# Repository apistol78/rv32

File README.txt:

TODO
----

- UART with QM-Tech board.
- Parallell LCD display with QM-Tech board.
- Audio on Terasic board.
- Audio on QM-Tech board.
- USB-host PICO.

STATS
-----

12264 (42%)

https://www.intel.com/content/dam/www/programmable/us/en/pdfs/literature/hb/external-memory/emi.pdf
https://itectec.com/electrical/electronic-alteras-dram-controller-with-uniphy/

https://mindchasers.com/dev/rv-getting-started

quake-k210

../configure --prefix=/opt/rv32-imf --with-arch=rv32imf --with-abi=ilp32

SDRAM
24 bit address
32 bit word

20000000 - 20FFFFFF

16777215 words

536870912 bytes => 512 MByte

Winbond SDRAM, W9825G6KH-6
W9864G6JT

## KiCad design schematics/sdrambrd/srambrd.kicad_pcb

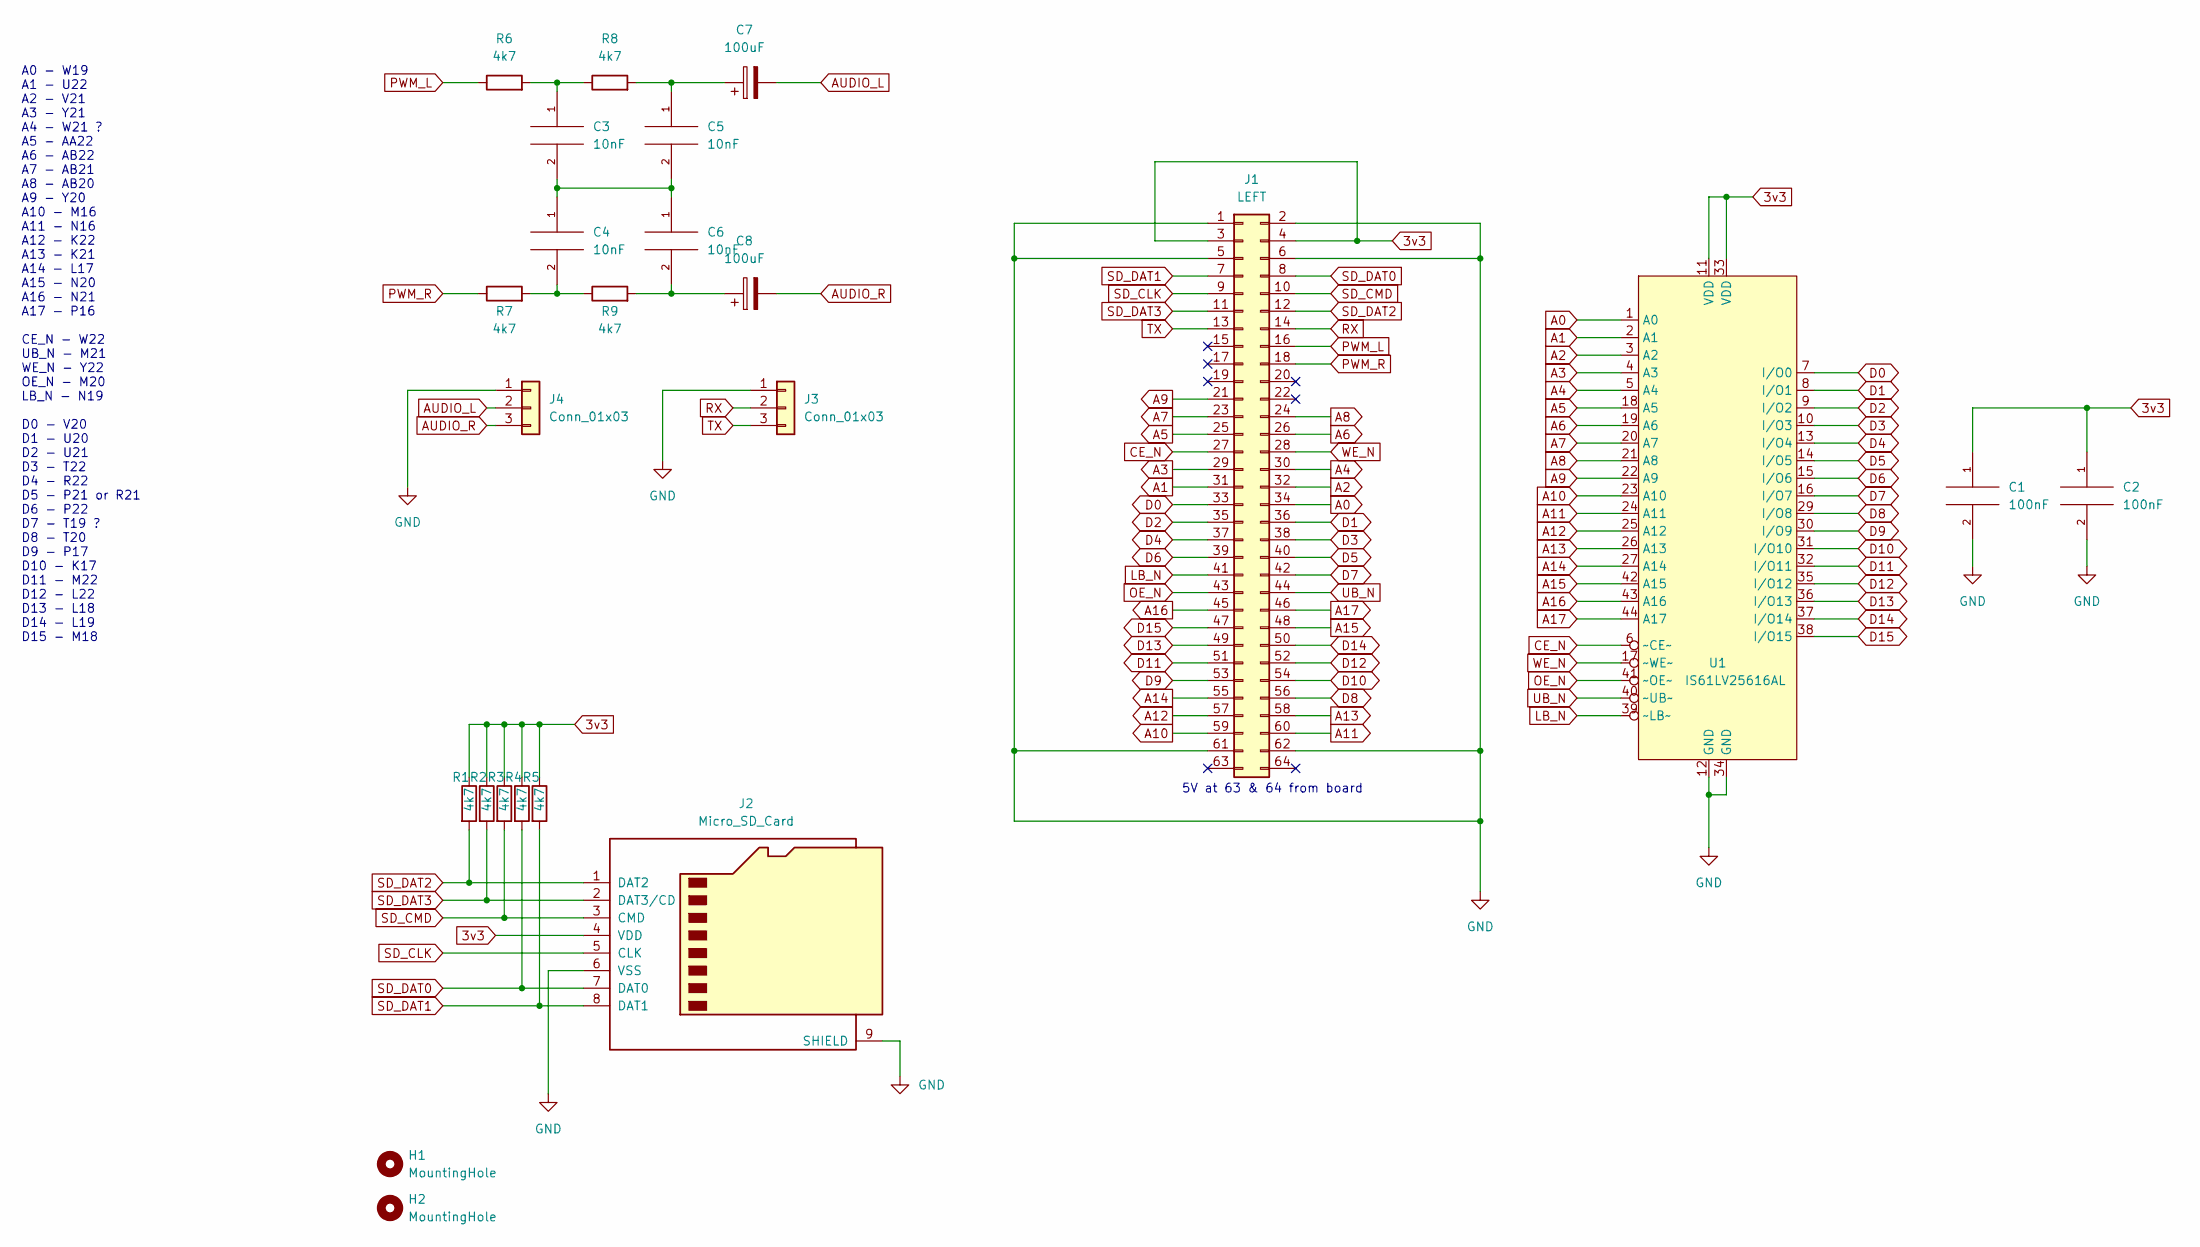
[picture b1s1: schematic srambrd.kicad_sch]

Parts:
C1, C2: 100nF; C_0805_2012Metric_Pad1.18x1.45mm_HandSolder
C3, C4, C5, C6: 10nF; C_0805_2012Metric_Pad1.18x1.45mm_HandSolder
C7, C8: 100uF; CP_Elec_5x5.3
H1, H2: MountingHole; MountingHole_3.2mm_M3_DIN965_Pad
J1: LEFT; PinSocket_2x32_P2.54mm_Vertical
J2: Micro_SD_Card; microSD_HC_Hirose_DM3D-SF
J3, J4: Conn_01x03; PinHeader_1x03_P2.54mm_Vertical
R1, R2, R3, R4, R5, R6, R7, R8, R9: 4k7; R_0805_2012Metric_Pad1.20x1.40mm_HandSolder
U1: IS61LV25616AL; TSOP-II-44_10.16x18.41mm_P0.8mm

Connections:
3v3: C1.1, C2.1, J1.3, J1.4, J2.4 (VDD), R1.1, R2.1, R3.1, R4.1, R5.1, U1.11 (VDD), U1.33 (VDD)
A0: J1.34, U1.1 (A0)
A1: J1.31, U1.2 (A1)
A2: J1.32, U1.3 (A2)
A3: J1.29, U1.4 (A3)
A4: J1.30, U1.5 (A4)
A5: J1.25, U1.18 (A5)
A6: J1.26, U1.19 (A6)
A7: J1.23, U1.20 (A7)
A8: J1.24, U1.21 (A8)
A9: J1.21, U1.22 (A9)
A10: J1.59, U1.23 (A10)
A11: J1.60, U1.24 (A11)
A12: J1.57, U1.25 (A12)
A13: J1.58, U1.26 (A13)
A14: J1.55, U1.27 (A14)
A15: J1.48, U1.42 (A15)
A16: J1.45, U1.43 (A16)
A17: J1.46, U1.44 (A17)
AUDIO_L: C7.2, J4.2
AUDIO_R: C8.2, J4.3
CE_N: J1.27, U1.6 (~CE~)
D0: J1.33, U1.7 (I/O0)
D1: J1.36, U1.8 (I/O1)
D2: J1.35, U1.9 (I/O2)
D3: J1.38, U1.10 (I/O3)
D4: J1.37, U1.13 (I/O4)
D5: J1.40, U1.14 (I/O5)
D6: J1.39, U1.15 (I/O6)
D7: J1.42, U1.16 (I/O7)
D8: J1.56, U1.29 (I/O8)
D9: J1.53, U1.30 (I/O9)
D10: J1.54, U1.31 (I/O10)
D11: J1.51, U1.32 (I/O11)
D12: J1.52, U1.35 (I/O12)
D13: J1.49, U1.36 (I/O13)
D14: J1.50, U1.37 (I/O14)
D15: J1.47, U1.38 (I/O15)
GND: C1.2, C2.2, J1.1, J1.2, J1.5, J1.6, J1.61, J1.62, J2.6 (VSS), J2.9 (SHIELD), J3.1, J4.1, U1.12 (GND), U1.34 (GND)
LB_N: J1.41, U1.39 (~LB~)
unnamed: C3.1, R6.2, R8.1
unnamed: C3.2, C4.1, C5.2, C6.1
unnamed: C4.2, R7.2, R9.1
unnamed: C5.1, C7.1, R8.2
unnamed: C6.2, C8.1, R9.2
OE_N: J1.43, U1.41 (~OE~)
PWM_L: J1.16, R6.1
PWM_R: J1.18, R7.1
RX: J1.14, J3.2
SD_CLK: J1.9, J2.5 (CLK)
SD_CMD: J1.10, J2.3 (CMD), R3.2
SD_DAT0: J1.8, J2.7 (DAT0), R4.2
SD_DAT1: J1.7, J2.8 (DAT1), R5.2
SD_DAT2: J1.12, J2.1 (DAT2), R1.2
SD_DAT3: J1.11, J2.2 (DAT3/CD), R2.2
TX: J1.13, J3.3
UB_N: J1.44, U1.40 (~UB~)
WE_N: J1.28, U1.17 (~WE~)

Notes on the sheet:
5V at 63 & 64 from board
A0 - W19 A1 - U22 A2 - V21 A3 - Y21 A4 - W21 ? A5 - AA22 A6 - AB22 A7 - AB21 A8 - AB20 A9 - Y20 A10 - M16 A11 - N16 A12 - K22 A13 - K21 A14 - L17 A15 - N20 A16 - N21 A17 - P16 CE_N - W22 UB_N - M21 WE_N - Y22 OE_N - M20 LB_N - N19 D0 - V20 D1 - U20 D2 - U21 D3 - T22 D4 - R22 D5 - P21 or R21 D6 - P2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

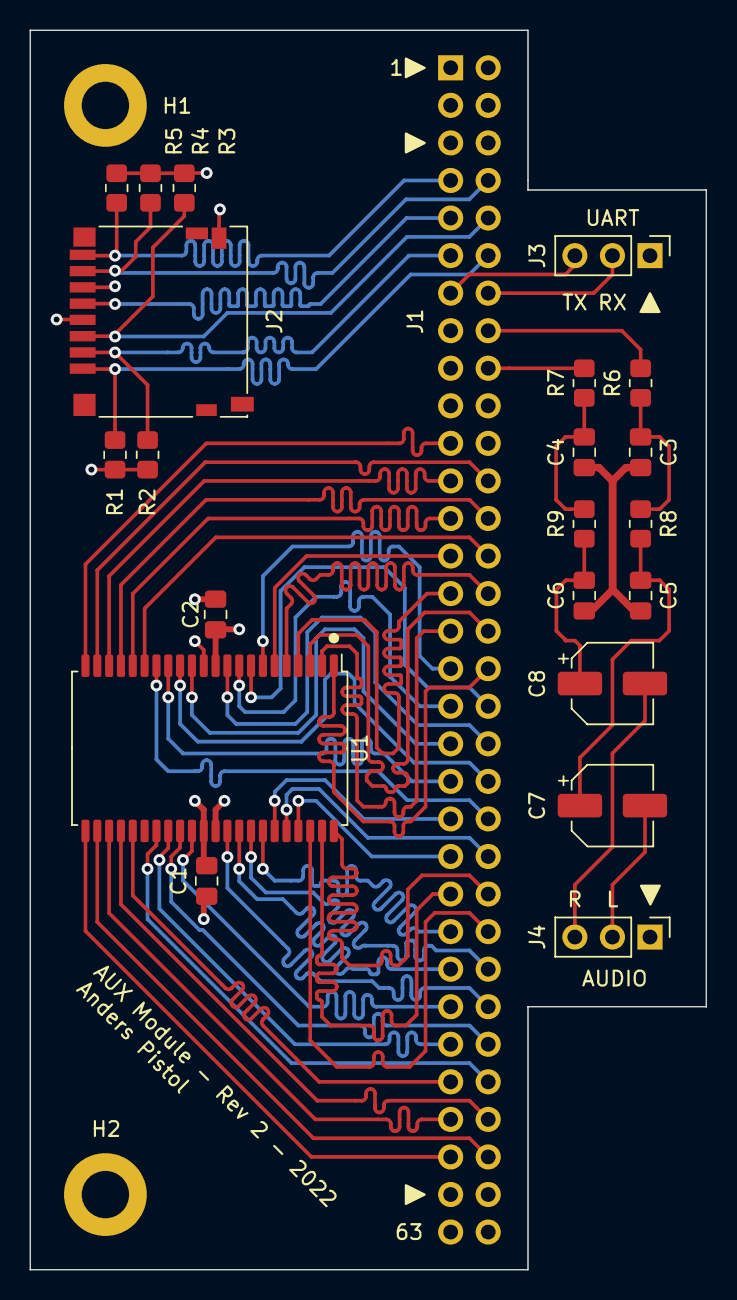
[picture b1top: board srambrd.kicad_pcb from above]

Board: 4 copper layers, 45.7 x 83.8 mm, 24 parts (1 on the bottom side), 58 nets.

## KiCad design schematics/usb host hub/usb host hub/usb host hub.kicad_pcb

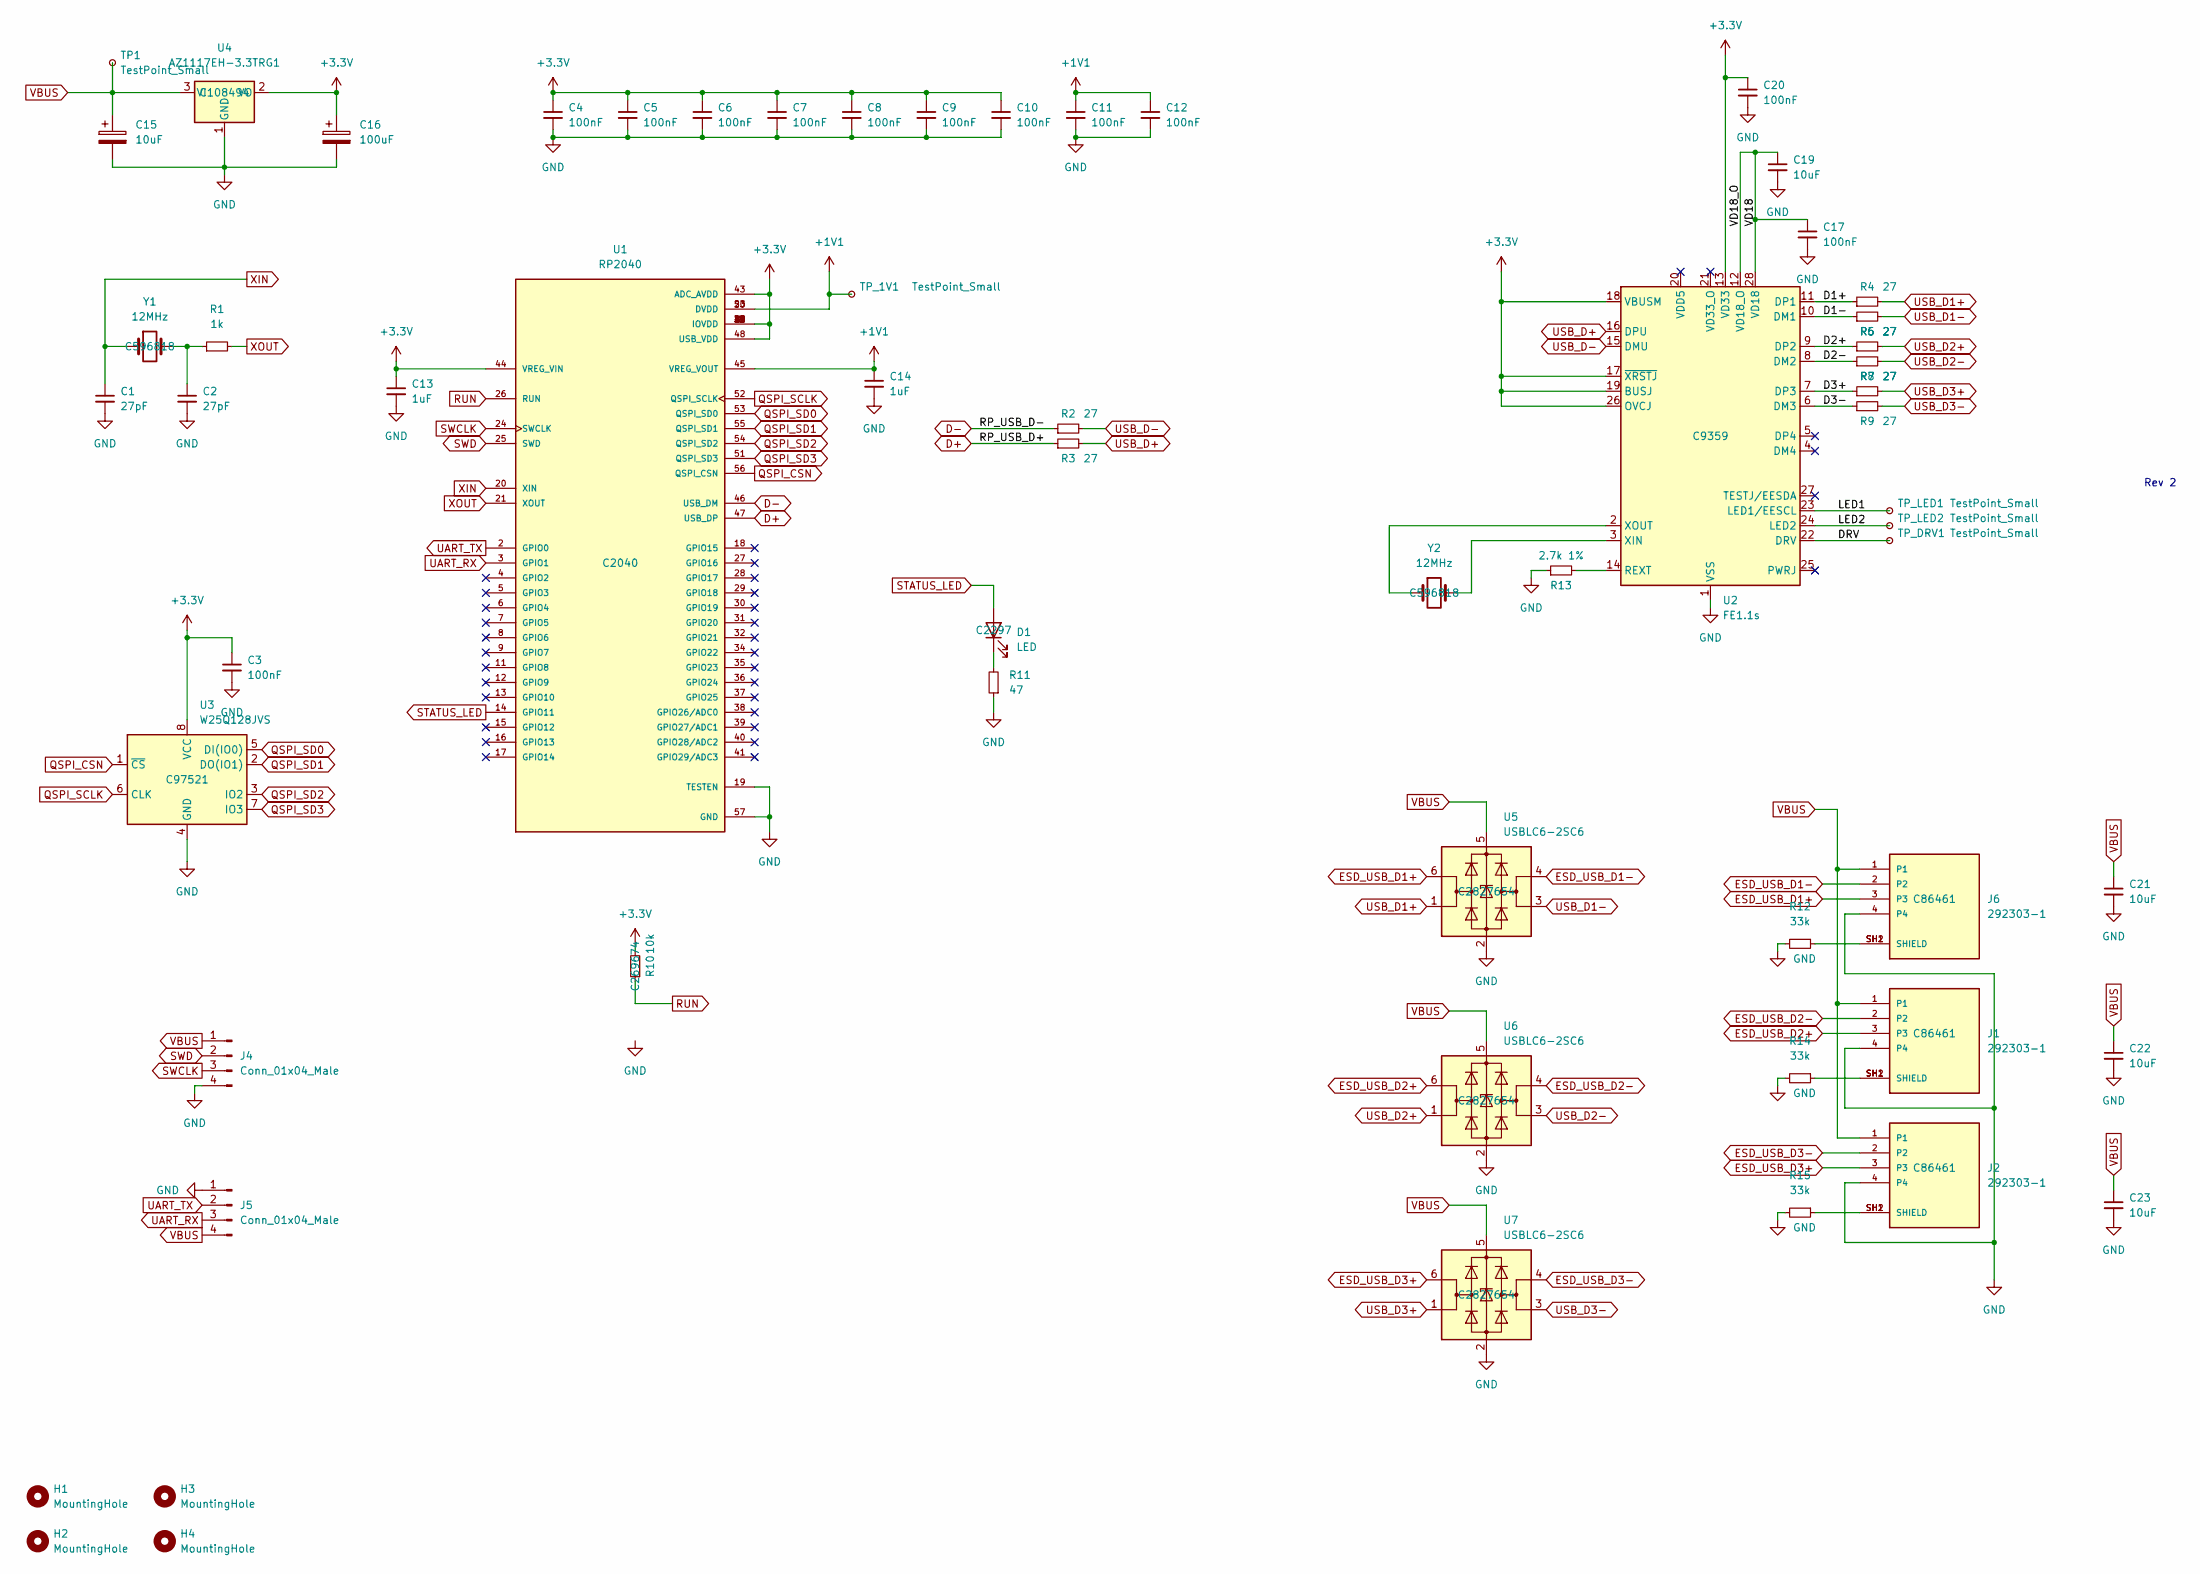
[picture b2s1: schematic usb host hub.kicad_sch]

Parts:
C1, C2: 27pF; C_0805_2012Metric
C3, C4, C5, C6, C7, C8, C9, C10, C11, C12, C17, C20: 100nF; C_0402_1005Metric; LCSC C307331
C13, C14: 1uF; C_0402_1005Metric
C15: 10uF; CP_Elec_5x5.3
C16: 100uF; CP_Elec_5x5.3
C19: 10uF; C_0402_1005Metric
C21, C22, C23: 10uF; C_0805_2012Metric
D1: LED; LED_0805_2012Metric; LCSC C2297
H1, H2, H3, H4: MountingHole; MountingHole_3.2mm_M3_DIN965_Pad
J1, J2, J6: 292303-1; TE_292303-1
J4: Conn_01x04_Male; PinHeader_1x04_P2.54mm_Vertical
J5: Conn_01x04_Male; JST_EH_B4B-EH-A_1x04_P2.50mm_Vertical
R1: 1k; R_0805_2012Metric
R2, R3: 27; R_0805_2012Metric
R4, R5, R6, R7, R8, R9: 27; R_0402_1005Metric
R10: 10k; R_0402_1005Metric; LCSC C269674
R11: 47; R_0805_2012Metric
R12, R14, R15: 33k; R_0805_2012Metric
R13: 2.7k 1%; R_0402_1005Metric; LCSC C25885
TP1: TestPoint_Small; TestPoint_Pad_D1.5mm
TP_1V1: TestPoint_Small; TestPoint_Pad_D1.5mm
TP_DRV1: TestPoint_Small; TestPoint_Pad_D1.5mm
TP_LED1, TP_LED2: TestPoint_Small; TestPoint_Pad_D1.5mm
U1: RP2040; QFN40P700X700X90-57N; PARTREV 1.6.1; LCSC C2040
U2: FE1.1s; SSOP-28_3.9x9.9mm_P0.635mm; LCSC C9359
U3: W25Q128JVS; SOIC-8_5.23x5.23mm_P1.27mm; LCSC C97521
U4: AZ1117EH-3.3TRG1; SOT-223-3_TabPin2; LCSC C108494
U5, U6, U7: USBLC6-2SC6; SOT-23-6
Y1, Y2: 12MHz; Crystal_SMD_HC49-SD

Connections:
+1V1: C11.1, C12.1, C14.1, TP_1V1.1, U1.23 (DVDD), U1.45 (VREG_VOUT), U1.50 (DVDD)
+3V3: C3.1, C4.1, C5.1, C6.1, C7.1, C8.1, C9.1, C10.1, C13.1, C16.1, C20.1, R10.2, U1.1 (IOVDD), U1.10 (IOVDD), U1.22 (IOVDD), U1.33 (IOVDD), U1.42 (IOVDD), U1.43 (ADC_AVDD), U1.44 (VREG_VIN), U1.48 (USB_VDD), U1.49 (IOVDD), U2.13 (VD33), U2.17 (~XRSTJ), U2.18 (VBUSM), U2.19 (BUSJ), U2.26 (OVCJ), U3.8 (VCC), U4.2 (VO)
/D1+: R4.1, U2.11 (DP1)
/D1-: R5.1, U2.10 (DM1)
/D2+: R6.1, U2.9 (DP2)
/D2-: R7.1, U2.8 (DM2)
/D3+: R8.1, U2.7 (DP3)
/D3-: R9.1, U2.6 (DM3)
/DRV: TP_DRV1.1, U2.22 (DRV)
/LED1: TP_LED1.1, U2.23 (LED1/EESCL)
/LED2: TP_LED2.1, U2.24 (LED2)
/VD18: C17.1, C19.1, U2.12 (VD18_O), U2.28 (VD18)
D+: R3.1, U1.47 (USB_DP)
D-: R2.1, U1.46 (USB_DM)
ESD_USB_D1+: J6.3, U5.6 (I/O1)
ESD_USB_D1-: J6.2, U5.4 (I/O2)
ESD_USB_D2+: J1.3, U6.6 (I/O1)
ESD_USB_D2-: J1.2, U6.4 (I/O2)
ESD_USB_D3+: J2.3, U7.6 (I/O1)
ESD_USB_D3-: J2.2, U7.4 (I/O2)
GND: C1.2, C2.2, C3.2, C4.2, C5.2, C6.2, C7.2, C8.2, C9.2, C10.2, C11.2, C12.2, C13.2, C14.2, C15.2, C16.2, C17.2, C19.2, C20.2, C21.2, C22.2, C23.2, J1.4, J2.4, J4.4, J5.1, J6.4, R11.1, R12.2, R13.1, R14.2, R15.2, U1.19 (TESTEN), U1.57 (GND), U2.1 (VSS), U3.4 (GND), U4.1 (GND), U5.2 (GND), U6.2 (GND), U7.2 (GND)
unnamed: C2.1, R1.1, Y1.2
unnamed: D1.1 (K), R11.2
unnamed: J1.SH1 (SHIELD), J1.SH2 (SHIELD), R14.1
unnamed: J2.SH1 (SHIELD), J2.SH2 (SHIELD), R15.1
unnamed: J6.SH1 (SHIELD), J6.SH2 (SHIELD), R12.1
unnamed: R13.2, U2.14 (REXT)
unnamed: U2.3 (XIN), Y2.2
unnamed: U2.2 (XOUT), Y2.1
QSPI_CSN: U1.56 (QSPI_CSN), U3.1 (~CS)
QSPI_SCLK: U1.52 (QSPI_SCLK), U3.6 (CLK)
QSPI_SD0: U1.53 (QSPI_SD0), U3.5 (DI(IO0))
QSPI_SD1: U1.55 (QSPI_SD1), U3.2 (DO(IO1))
QSPI_SD2: U1.54 (QSPI_SD2), U3.3 (IO2)
QSPI_SD3: U1.51 (QSPI_SD3), U3.7 (IO3)
RUN: R10.1, U1.26 (RUN)
STATUS_LED: D1.2 (A), U1.14 (GPIO11)
SWCLK: J4.3, U1.24 (SWCLK)
SWD: J4.2, U1.25 (SWD)
UART_RX: J5.3, U1.3 (GPIO1)
UART_TX: J5.2, U1.2 (GPIO0)
USB_D1+: R4.2, U5.1 (I/O1)
USB_D1-: R5.2, U5.3 (I/O2)
USB_D2+: R6.2, U6.1 (I/O1)
USB_D2-: R7.2, U6.3 (I/O2)
USB_D3+: R8.2, U7.1 (I/O1)
USB_D3-: R9.2, U7.3 (I/O2)
USB_D+: R3.2, U2.16 (DPU)
USB_D-: R2.2, U2.15 (DMU)
VBUS: C15.1, C21.1, C22.1, C23.1, J1.1, J2.1, J4.1, J5.4, J6.1, TP1.1, U4.3 (VI), U5.5 (VBUS), U6.5 (VBUS), U7.5 (VBUS)
XIN: C1.1, U1.20 (XIN), Y1.1
XOUT: R1.2, U1.21 (XOUT)

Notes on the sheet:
Rev 2

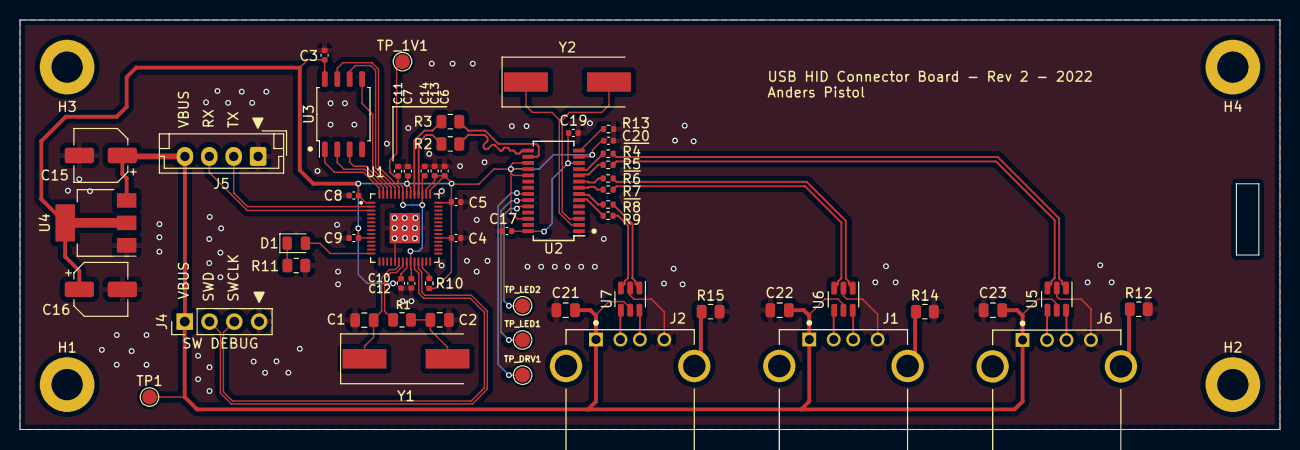
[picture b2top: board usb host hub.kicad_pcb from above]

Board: 2 copper layers, 129.0 x 41.9 mm, 61 parts (0 on the bottom side), 52 nets.

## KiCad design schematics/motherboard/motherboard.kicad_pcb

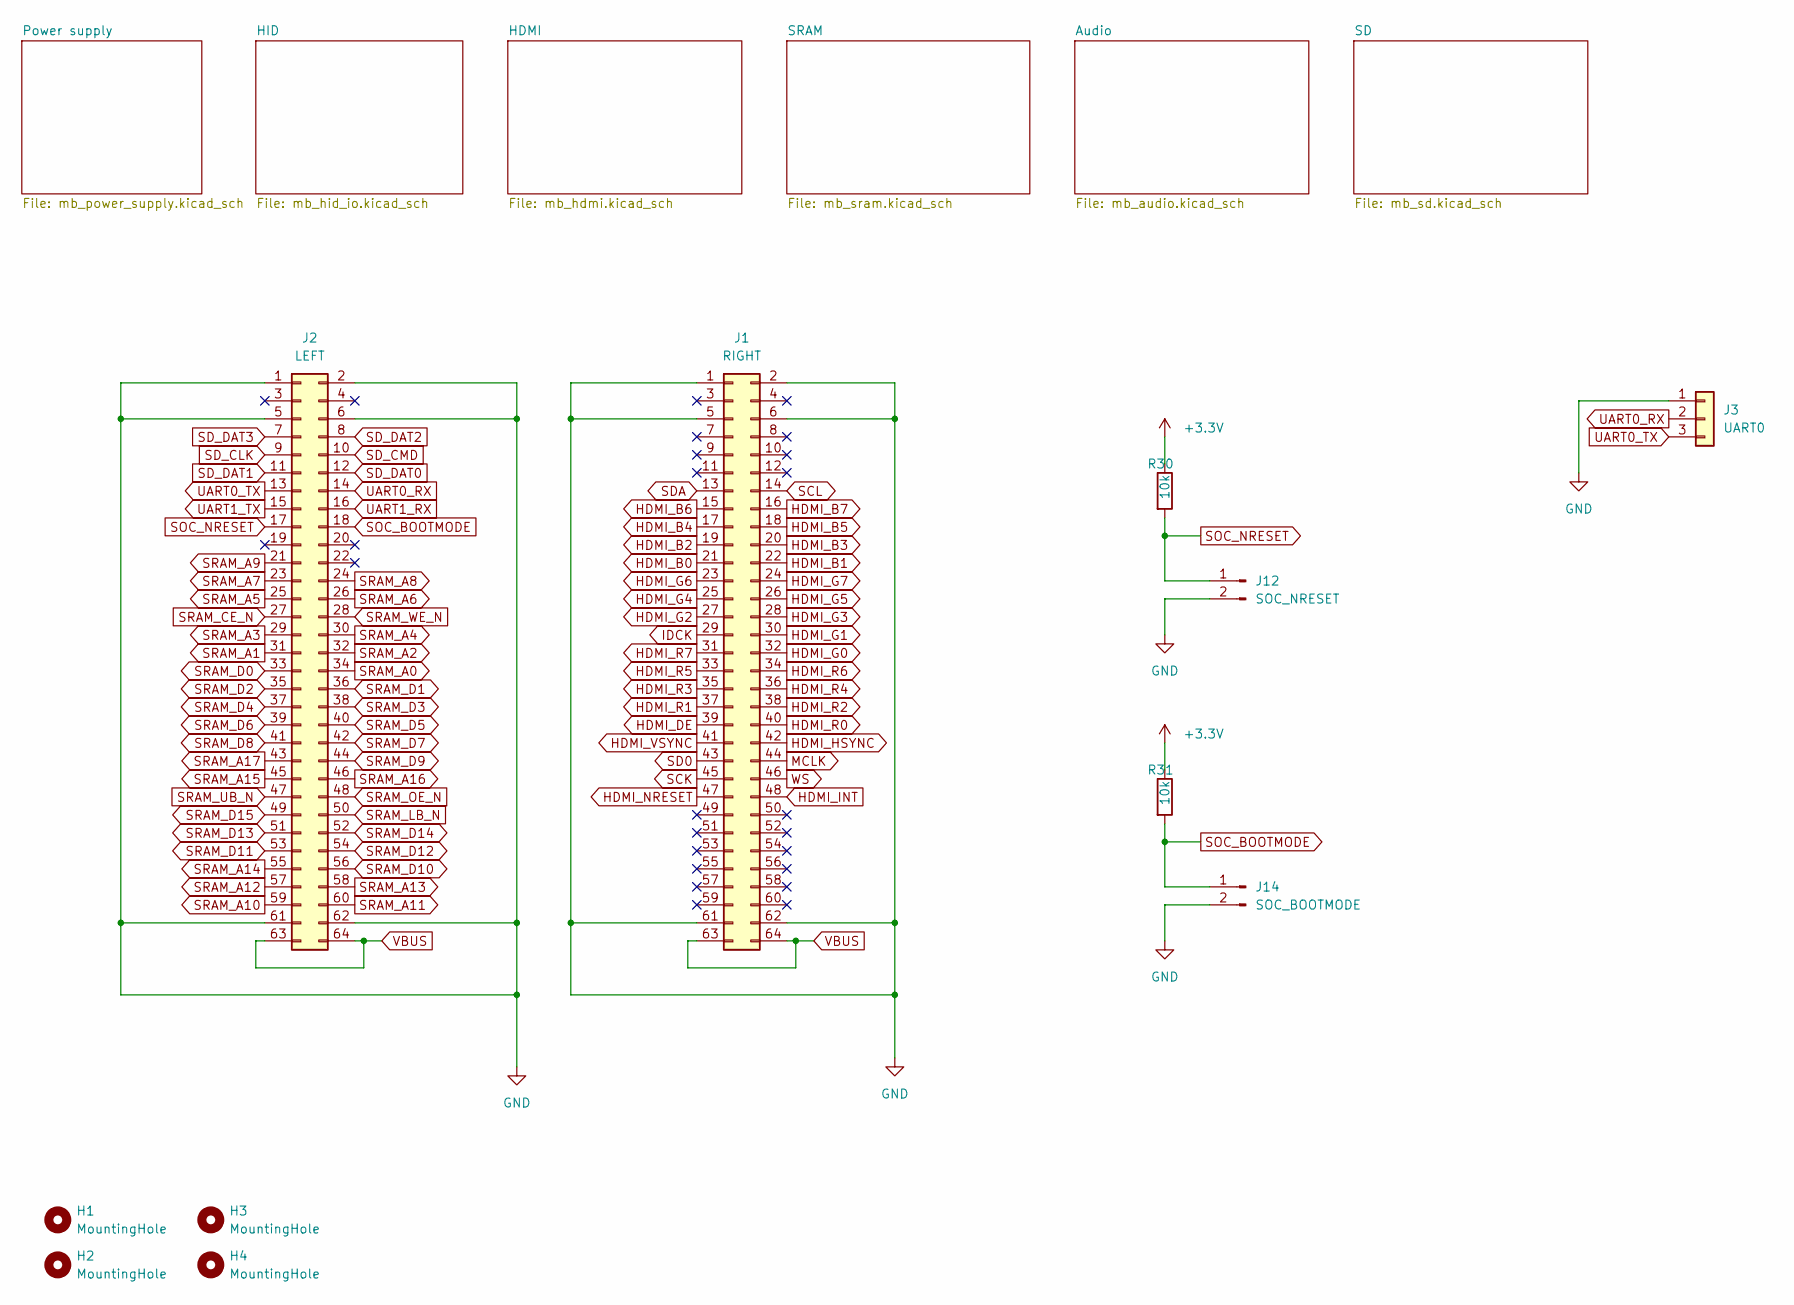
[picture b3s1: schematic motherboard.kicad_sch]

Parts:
H1, H2, H3, H4: MountingHole; MountingHole_3.2mm_M3_Pad_Via
J1: RIGHT; PinSocket_2x32_P2.54mm_Vertical
J2: LEFT; PinSocket_2x32_P2.54mm_Vertical
J3: UART0; PinHeader_1x03_P2.54mm_Vertical
J12: SOC_NRESET; PinHeader_1x02_P2.54mm_Vertical
J14: SOC_BOOTMODE; PinHeader_1x02_P2.54mm_Vertical
R30, R31: 10k; R_0805_2012Metric_Pad1.20x1.40mm_HandSolder

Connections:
+3V3: R30.1, R31.1; also elsewhere on the board
GND: J1.1, J1.2, J1.5, J1.6, J1.61, J1.62, J2.1, J2.2, J2.5, J2.6, J2.61, J2.62, J3.1, J12.2, J14.2; also elsewhere on the board
HDMI_B0: J1.21; also elsewhere on the board
HDMI_B1: J1.22; also elsewhere on the board
HDMI_B2: J1.19; also elsewhere on the board
HDMI_B3: J1.20; also elsewhere on the board
HDMI_B4: J1.17; also elsewhere on the board
HDMI_B5: J1.18; also elsewhere on the board
HDMI_B6: J1.15; also elsewhere on the board
HDMI_B7: J1.16; also elsewhere on the board
HDMI_DE: J1.39; also elsewhere on the board
HDMI_G0: J1.32; also elsewhere on the board
HDMI_G1: J1.30; also elsewhere on the board
HDMI_G2: J1.27; also elsewhere on the board
HDMI_G3: J1.28; also elsewhere on the board
HDMI_G4: J1.25; also elsewhere on the board
HDMI_G5: J1.26; also elsewhere on the board
HDMI_G6: J1.23; also elsewhere on the board
HDMI_G7: J1.24; also elsewhere on the board
HDMI_HSYNC: J1.42; also elsewhere on the board
HDMI_INT: J1.48; also elsewhere on the board
HDMI_NRESET: J1.47; also elsewhere on the board
HDMI_R0: J1.40; also elsewhere on the board
HDMI_R1: J1.37; also elsewhere on the board
HDMI_R2: J1.38; also elsewhere on the board
HDMI_R3: J1.35; also elsewhere on the board
HDMI_R4: J1.36; also elsewhere on the board
HDMI_R5: J1.33; also elsewhere on the board
HDMI_R6: J1.34; also elsewhere on the board
HDMI_R7: J1.31; also elsewhere on the board
HDMI_VSYNC: J1.41; also elsewhere on the board
IDCK: J1.29; also elsewhere on the board
MCLK: J1.44; also elsewhere on the board
SCK: J1.45; also elsewhere on the board
SCL: J1.14; also elsewhere on the board
SD0: J1.43; also elsewhere on the board
SDA: J1.13; also elsewhere on the board
SD_CLK: J2.9; also elsewhere on the board
SD_CMD: J2.10; also elsewhere on the board
SD_DAT0: J2.12; also elsewhere on the board
SD_DAT1: J2.11; also elsewhere on the board
SD_DAT2: J2.8; also elsewhere on the board
SD_DAT3: J2.7; also elsewhere on the board
SOC_BOOTMODE: J2.18, J14.1, R31.2
SOC_NRESET: J2.17, J12.1, R30.2
SRAM_A0: J2.34; also elsewhere on the board
SRAM_A1: J2.31; also elsewhere on the board
SRAM_A2: J2.32; also elsewhere on the board
SRAM_A3: J2.29; also elsewhere on the board
SRAM_A4: J2.30; also elsewhere on the board
SRAM_A5: J2.25; also elsewhere on the board
SRAM_A6: J2.26; also elsewhere on the board
SRAM_A7: J2.23; also elsewhere on the board
SRAM_A8: J2.24; also elsewhere on the board
SRAM_A9: J2.21; also elsewhere on the board
SRAM_A10: J2.59; also elsewhere on the board
SRAM_A11: J2.60; also elsewhere on the board
SRAM_A12: J2.57; also elsewhere on the board
SRAM_A13: J2.58; also elsewhere on the board
SRAM_A14: J2.55; also elsewhere on the board
SRAM_A15: J2.45; also elsewhere on the board
SRAM_A16: J2.46; also elsewhere on the board
SRAM_A17: J2.43; also elsewhere on the board
SRAM_CE_N: J2.27; also elsewhere on the board
SRAM_D0: J2.33; also elsewhere on the board
SRAM_D1: J2.36; also elsewhere on the board
SRAM_D2: J2.35; also elsewhere on the board
SRAM_D3: J2.38; also elsewhere on the board
SRAM_D4: J2.37; also elsewhere on the board
SRAM_D5: J2.40; also elsewhere on the board
SRAM_D6: J2.39; also elsewhere on the board
SRAM_D7: J2.42; also elsewhere on the board
SRAM_D8: J2.41; also elsewhere on the board
SRAM_D9: J2.44; also elsewhere on the board
SRAM_D10: J2.56; also elsewhere on the board
SRAM_D11: J2.53; also elsewhere on the board
SRAM_D12: J2.54; also elsewhere on the board
SRAM_D13: J2.51; also elsewhere on the board
SRAM_D14: J2.52; also elsewhere on the board
SRAM_D15: J2.49; also elsewhere on the board
SRAM_LB_N: J2.50; also elsewhere on the board
SRAM_OE_N: J2.48; also elsewhere on the board
SRAM_UB_N: J2.47; also elsewhere on the board
SRAM_WE_N: J2.28; also elsewhere on the board
UART0_RX: J2.14, J3.2
UART0_TX: J2.13, J3.3
UART1_RX: J2.16; also elsewhere on the board
UART1_TX: J2.15; also elsewhere on the board
VBUS: J1.63, J1.64, J2.63, J2.64; also elsewhere on the board
WS: J1.46; also elsewhere on the board

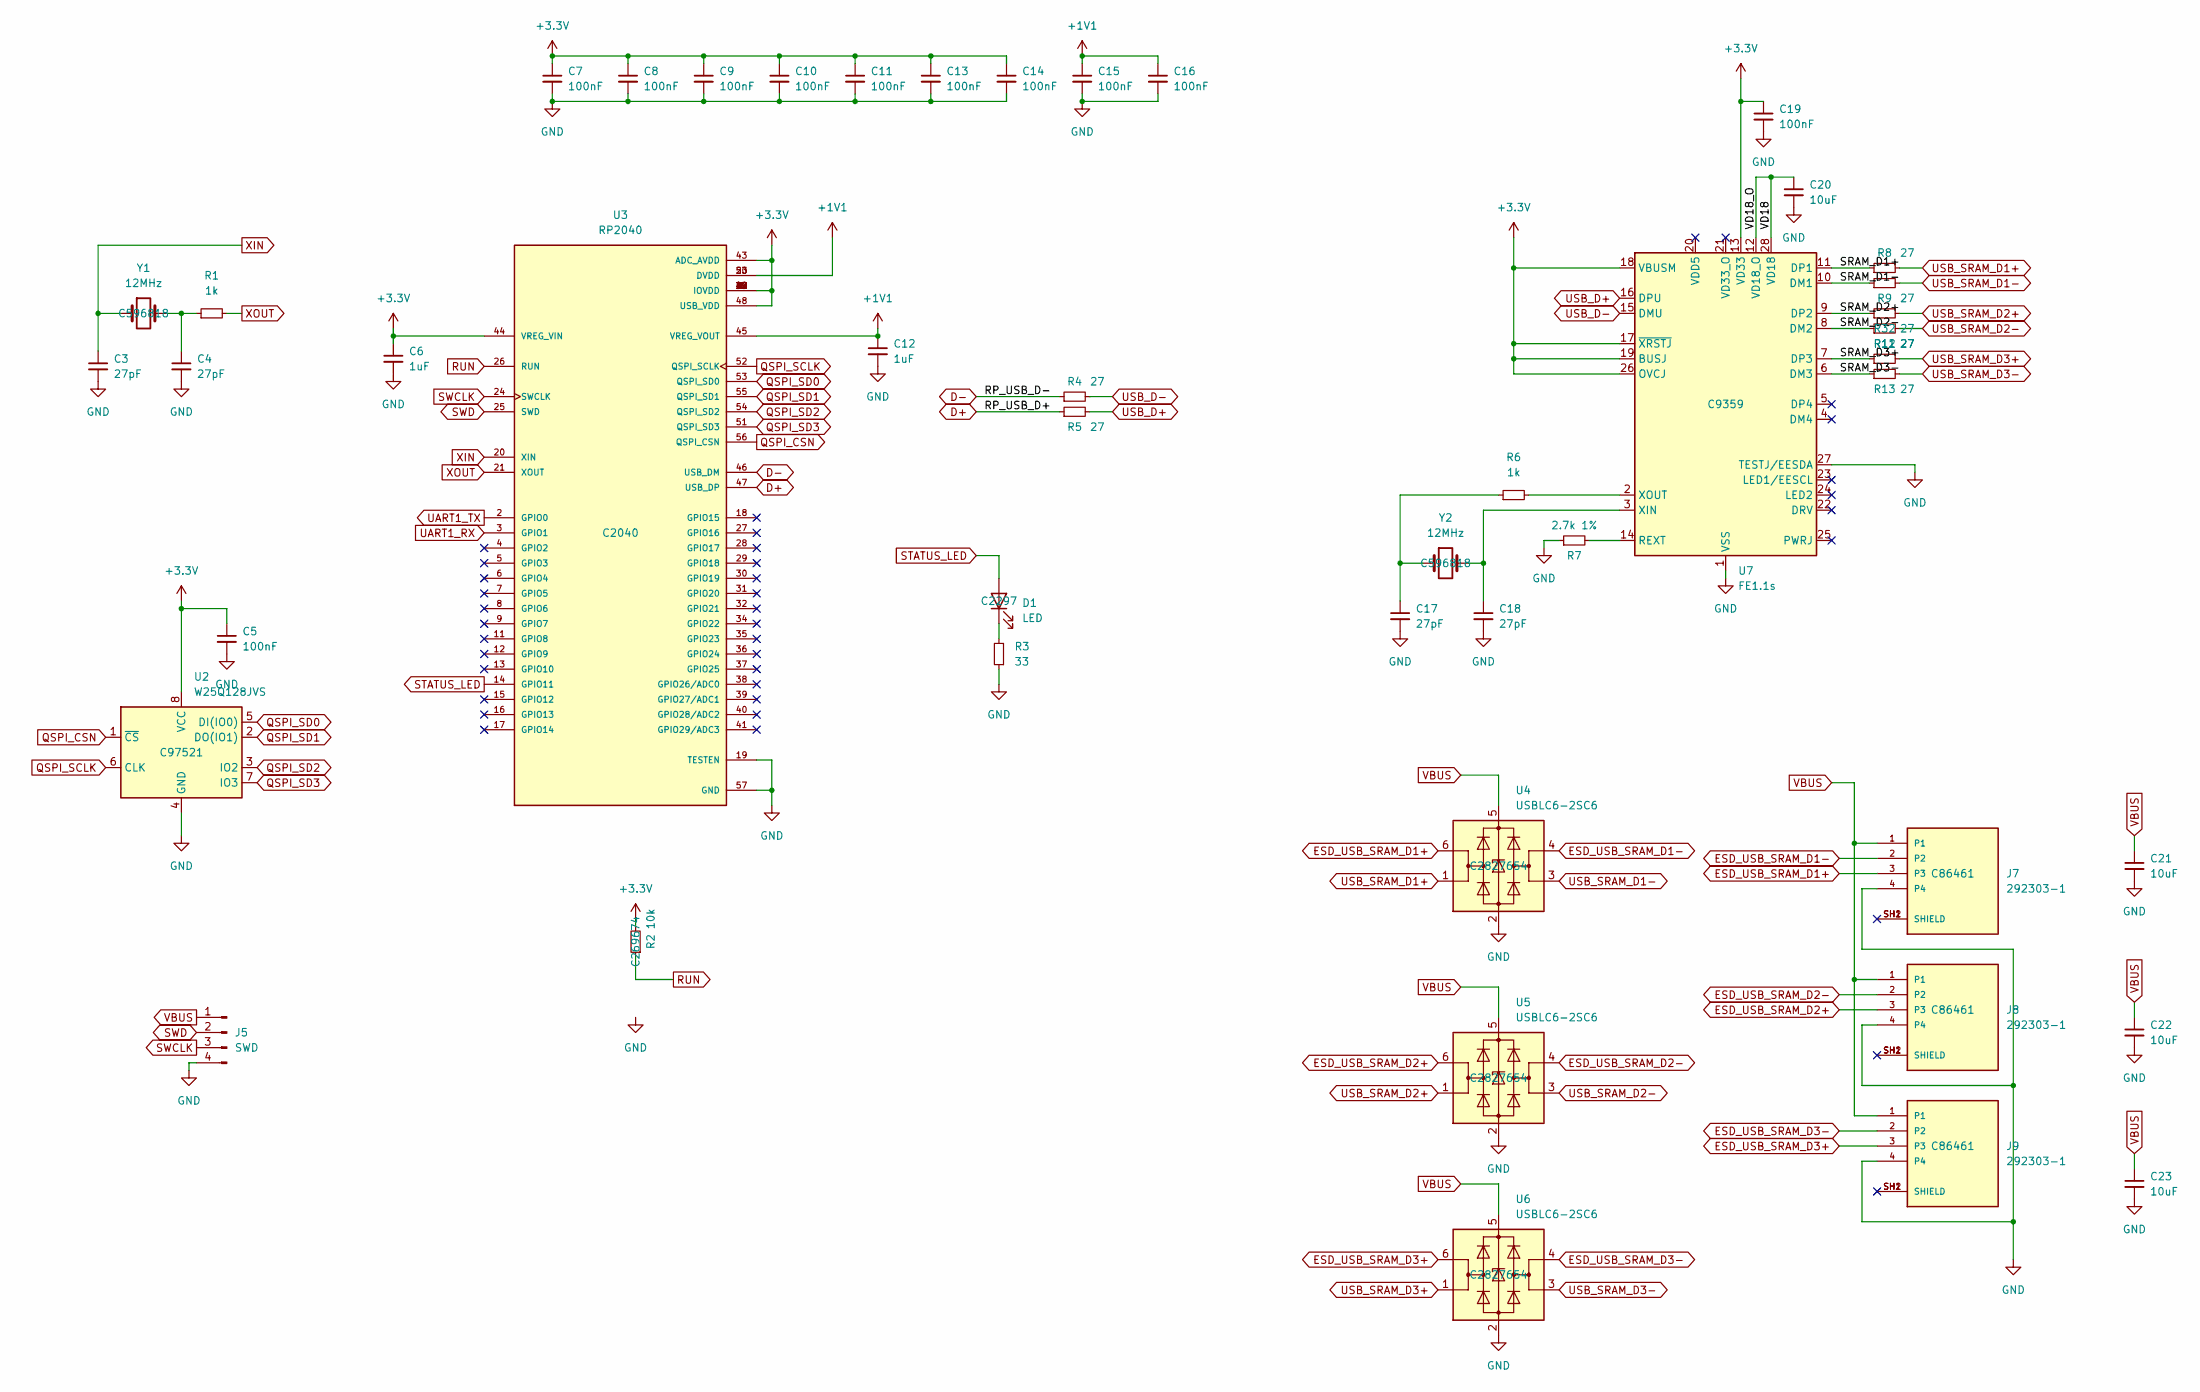
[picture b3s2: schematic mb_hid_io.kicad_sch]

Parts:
C3, C4, C17, C18: 27pF; C_0805_2012Metric
C5, C7, C8, C9, C10, C11, C13, C14, C15, C16, C19: 100nF; C_0402_1005Metric; LCSC C307331
C6, C12: 1uF; C_0402_1005Metric
C20: 10uF; C_0402_1005Metric
C21, C22, C23: 10uF; C_0805_2012Metric
D1: LED; LED_0805_2012Metric; LCSC C2297
J5: SWD; PinHeader_1x04_P2.54mm_Vertical
J7, J8, J9: 292303-1; TE_292303-1
R1, R6: 1k; R_0805_2012Metric
R2: 10k; R_0402_1005Metric; LCSC C269674
R3: 33; R_0805_2012Metric
R4, R5: 27; R_0805_2012Metric
R7: 2.7k 1%; R_0402_1005Metric; LCSC C25885
R8, R9, R11, R12, R13, R32: 27; R_0402_1005Metric
U2: W25Q128JVS; SOIC-8_5.23x5.23mm_P1.27mm; LCSC C97521
U3: RP2040; QFN40P700X700X90-57N; PARTREV 1.6.1; LCSC C2040
U4, U5, U6: USBLC6-2SC6; SOT-23-6
U7: FE1.1s; SSOP-28_3.9x9.9mm_P0.635mm; LCSC C9359
Y1, Y2: 12MHz; Crystal_SMD_HC49-SD

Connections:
+1V1: C12.1, C15.1, C16.1, U3.23 (DVDD), U3.45 (VREG_VOUT), U3.50 (DVDD)
+3V3: C5.1, C6.1, C7.1, C8.1, C9.1, C10.1, C11.1, C13.1, C14.1, C19.1, R2.2, U2.8 (VCC), U3.1 (IOVDD), U3.10 (IOVDD), U3.22 (IOVDD), U3.33 (IOVDD), U3.42 (IOVDD), U3.43 (ADC_AVDD), U3.44 (VREG_VIN), U3.48 (USB_VDD), U3.49 (IOVDD), U7.13 (VD33), U7.17 (~XRSTJ), U7.18 (VBUSM), U7.19 (BUSJ), U7.26 (OVCJ); also elsewhere on the board
/HID/SRAM_D1+: R8.1, U7.11 (DP1)
/HID/SRAM_D1-: R9.1, U7.10 (DM1)
/HID/SRAM_D2+: R32.1, U7.9 (DP2)
/HID/SRAM_D2-: R11.1, U7.8 (DM2)
/HID/SRAM_D3+: R12.1, U7.7 (DP3)
/HID/SRAM_D3-: R13.1, U7.6 (DM3)
/HID/VD18: C20.1, U7.12 (VD18_O), U7.28 (VD18)
D+: R5.1, U3.47 (USB_DP)
D-: R4.1, U3.46 (USB_DM)
ESD_USB_SRAM_D1+: J7.3, U4.6 (I/O1)
ESD_USB_SRAM_D1-: J7.2, U4.4 (I/O2)
ESD_USB_SRAM_D2+: J8.3, U5.6 (I/O1)
ESD_USB_SRAM_D2-: J8.2, U5.4 (I/O2)
ESD_USB_SRAM_D3+: J9.3, U6.6 (I/O1)
ESD_USB_SRAM_D3-: J9.2, U6.4 (I/O2)
GND: C3.2, C4.2, C5.2, C6.2, C7.2, C8.2, C9.2, C10.2, C11.2, C12.2, C13.2, C14.2, C15.2, C16.2, C17.2, C18.2, C19.2, C20.2, C21.2, C22.2, C23.2, J5.4, J7.4, J8.4, J9.4, R3.1, R7.1, U2.4 (GND), U3.19 (TESTEN), U3.57 (GND), U4.2 (GND), U5.2 (GND), U6.2 (GND), U7.1 (VSS), U7.27 (TESTJ/EESDA); also elsewhere on the board
unnamed: C4.1, R1.1, Y1.2
unnamed: C17.1, R6.1, Y2.1
unnamed: C18.1, U7.3 (XIN), Y2.2
unnamed: D1.1 (K), R3.2
unnamed: R6.2, U7.2 (XOUT)
unnamed: R7.2, U7.14 (REXT)
QSPI_CSN: U2.1 (~CS), U3.56 (QSPI_CSN)
QSPI_SCLK: U2.6 (CLK), U3.52 (QSPI_SCLK)
QSPI_SD0: U2.5 (DI(IO0)), U3.53 (QSPI_SD0)
QSPI_SD1: U2.2 (DO(IO1)), U3.55 (QSPI_SD1)
QSPI_SD2: U2.3 (IO2), U3.54 (QSPI_SD2)
QSPI_SD3: U2.7 (IO3), U3.51 (QSPI_SD3)
RUN: R2.1, U3.26 (RUN)
STATUS_LED: D1.2 (A), U3.14 (GPIO11)
SWCLK: J5.3, U3.24 (SWCLK)
SWD: J5.2, U3.25 (SWD)
UART1_RX: U3.3 (GPIO1); also elsewhere on the board
UART1_TX: U3.2 (GPIO0); also elsewhere on the board
USB_D+: R5.2, U7.16 (DPU)
USB_D-: R4.2, U7.15 (DMU)
USB_SRAM_D1+: R8.2, U4.1 (I/O1)
USB_SRAM_D1-: R9.2, U4.3 (I/O2)
USB_SRAM_D2+: R32.2, U5.1 (I/O1)
USB_SRAM_D2-: R11.2, U5.3 (I/O2)
USB_SRAM_D3+: R12.2, U6.1 (I/O1)
USB_SRAM_D3-: R13.2, U6.3 (I/O2)
VBUS: C21.1, C22.1, C23.1, J5.1, J7.1, J8.1, J9.1, U4.5 (VBUS), U5.5 (VBUS), U6.5 (VBUS); also elsewhere on the board
XIN: C3.1, U3.20 (XIN), Y1.1
XOUT: R1.2, U3.21 (XOUT)

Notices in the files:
board/SDRAM/SDRAM_tb.qsf:
Copyright (C) 2021  Intel Corporation. All rights reserved.
parts and their libraries:
Copyright 2021 Accelerated Designs. All rights reserved.
